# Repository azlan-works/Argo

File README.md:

# Argo v2

## Crowdsupply:

Argo is soon to launch on CrowdSupply, sign up now to be updated as soon as it's live and ready for pre-order!

https://www.crowdsupply.com/azlan-works/argo-cm5

## Mainboard
The main board houses the CM5 and breaks out the most basic functionality needed.

- 2x 100pin Hirose Connectors
- 2x MIPI-DSI/CSI
- 1x Micro-HDMI
- 1x HDMI FPC connector for external break out
- 1x PCIe FPC connector, Pi 5 compatible
- 2x USB-C (One for power/flashing - USB 2.0 and one regular USB 3.0)
- Integrated BMS (BQ25895) with up to 5A charging dependent on battery used.
- TPS61022 5V boost for upto 3A of constant power from battery or USB.
- I2C control for BQ25895 with ADC battery level monitoring.
- Onboard LSM6DSV16XTR IMU via I2C

Read more about the mainboard [here](./mainboard.md)
## Benchmarks:

Benchmarks conducted using v1 boards using CM5 16GB RAM and 64GB eMMC + Waveshare CM5 cooler with fan.

### On Adapter:

### On Battery:

## Expansion Boards:

### M.2 PCIe Expansion:
- Adds an M.2 M-Key Slot for external SSD
Read more about the SSD board [here](./ssdboard.md)

### Impedance Calculations:

### OSHWA Certification:

## Sponsored by OSHWLab Stars:
 &nbsp;

 </br>
 </br>
 
   &nbsp; &nbsp; &nbsp; &nbsp; &nbsp;  
 &nbsp;
  &nbsp;
   &nbsp;

</br></br>

Huge thanks to Bob from OSHWLab for all the support and sponsoring the PCBA! 

## Note:

Commerical reproduction is NOT permitted for this design without prior agreements.

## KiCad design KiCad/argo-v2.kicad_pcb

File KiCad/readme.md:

This KiCad project is just an export of the OSHWLab project, details may not match 100%

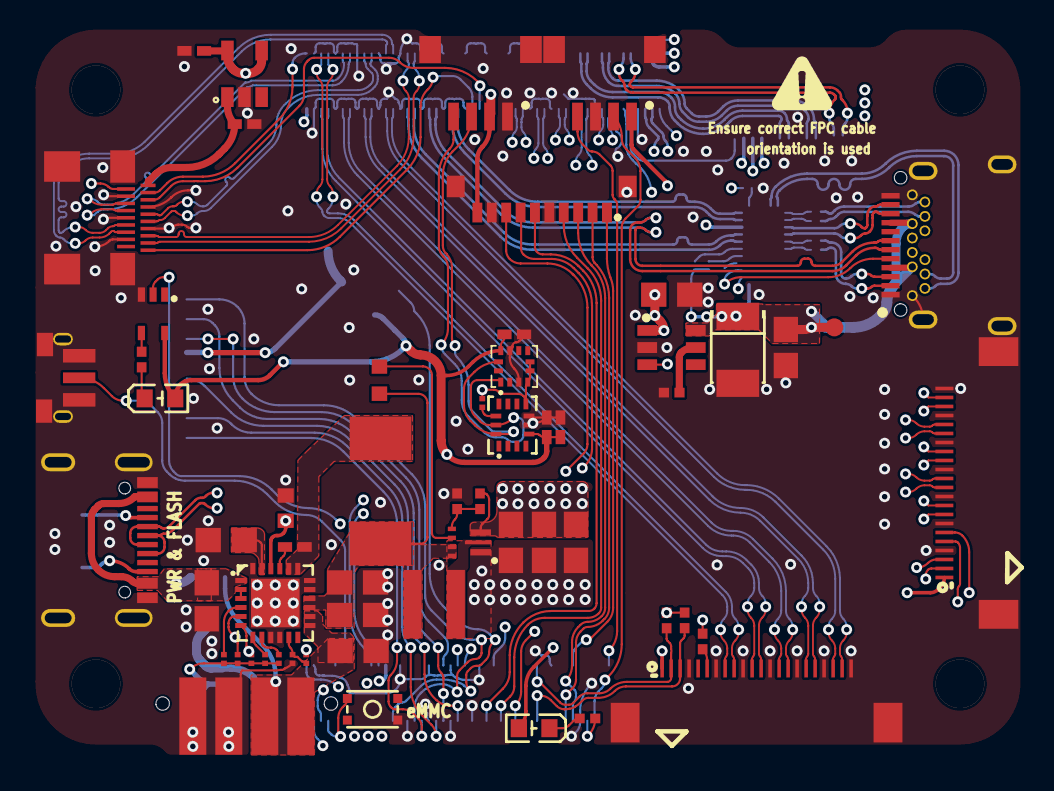
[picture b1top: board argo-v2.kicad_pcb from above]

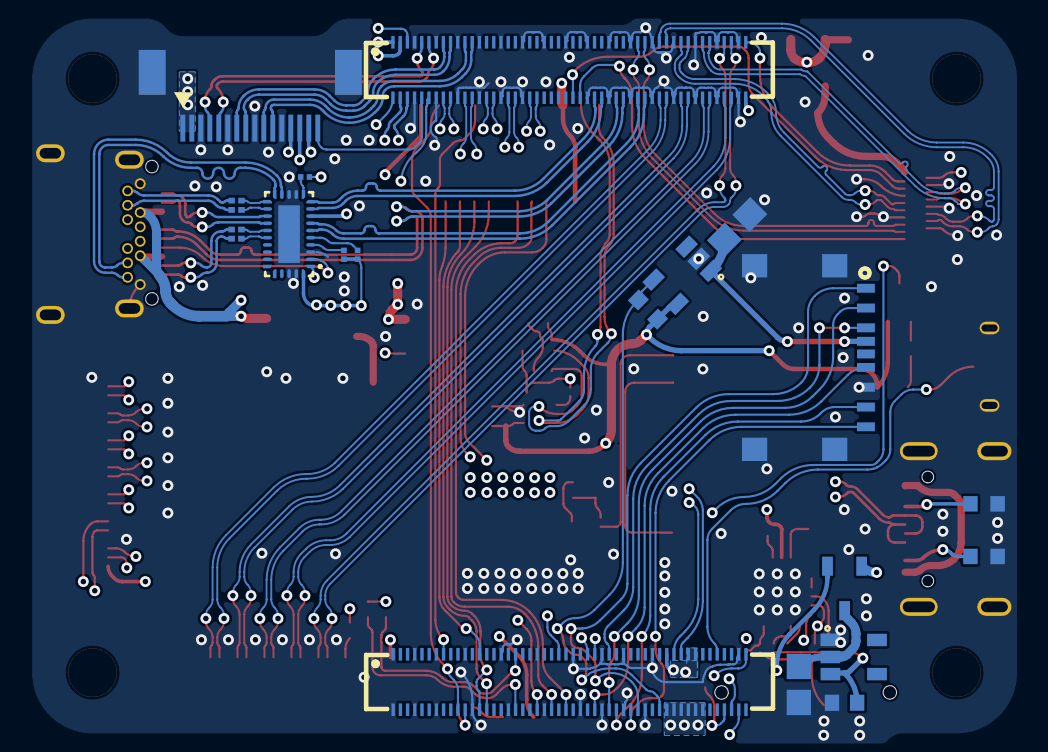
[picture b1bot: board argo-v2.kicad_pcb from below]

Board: 6 copper layers, 79 parts (22 on the bottom side), 127 nets.

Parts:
C1, C2, C30, C51, C52, C55, C58, C66, C69, C74, C75, C76: C0805
C3, C59: C0603
C4, C40, C41, C77, C78, C81: C0402
C53: CASE-B_3528
C70, C71, C72, C73: C0201
CN1, CN2: CONN-SMD_DF40HC-3.0-100DS-0.4V-51
CN6: CONN-SMD_GT-BTR20004-0250A-005A
D2: SOT-23-3_L2.9-W1.6-P1.90-LS2.8-BR
DPHY1, DPHY2: FPC-SMD_22P-P0.50_FH12-22S-0.5SH-55
FAN: CONN-SMD_4P-P1.00_SM04B-SRSS-TB-LF-SN
HDMI1: HDMI-SMD_HDMI-101W
I2C: CONN-SMD_4P-P1.00_SM04B-SRSS-TB-LF-SN
L1: IND-SMD_L6.5-W6.5_IHLP-2525
LED1: LED0603-FD
MODULE1: CM5IO{colon}Raspberry-Pi-5-Compute-Module
PCIe: FPC-SMD_16P-P0.50_HC-FPC-05-20-16RLTAG
PWR: USB-C-SMD_TYPEC-304J-BCP16
R6, R7, R12, R50: R0603
R29, R30, R31, R32, R34, R38, R51, R52: R0402
R39, R40, R41, R42, R43, R44, R45, R46, R47, R48, R53: R0201
SD-CARD: TF-SMD_TF-123-ARP9H15
SPI: CONN-SMD_10P-P0.80_HDGC0802WV-S-10P
SW2: KEY-SMD_4P-L2.8-W2.0-P1.20-LS3.0-TL
SW3: KEY-SMD_TS35CA-100GF-031
U7, U11, U13: TSOT-23-5_L2.9-W1.6-P0.95-LS2.8-BR
U9: QFN-24_L4.0-W4.0-P0.50-TL-EP2.7
U12: SOT-23-6_L2.9-W1.6-P0.95-LS2.8-BR
U14: LED0603-FD
U16: SC-88A_L2.0-W1.3-P0.65-LS2.1-BL
U20: VQFN-7_L2.0-W2.0-P0.55-TL_RWU
U21: IND-SMD_L4.1-W4.1_PA5430
U22: WQFN-30_L4.5-W2.5-P0.4-BL-EP
U23: LGA-14_L3.0-W2.5-P0.50-BR
U24: LGA-12_L2.0-W2.0-P0.50-BL
USB-C3.0: USB-C-SMD_TYPEC-324-BCP24

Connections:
$1N10774: R29.2, U14.2
$1N12706: R34.1, U16.4
$1N12751: LED1.2, R34.2
$2N4744: C4.1, U9.21
$2N5637: R44.2, R45.1, U9.11
$2N10575: U9.2, U9.3
$2N18023: C55.2, U9.23
$2N19126: PWR.A5, R6.1
$2N19130: PWR.B5, R7.1
$2N22099: R43.2, U9.8
$2N22411: C58.1, D2.3, U13.2
$2N49032: C4.2, L1.1, U9.19, U9.20
$2N49283: U20.2, U21.1
$2N51141: R50.1, U20.5
$2N51424: R38.2, R52.2, U20.4
$3N4264: DPHY2.6, R30.2
$4N5235: C41.2, HDMI1.19, U11.1
$4N37129: R53.1, U23.12
$5N11984: R51.1, U12.5
$5N17176: R46.1, U22.11
$5N17396: C73.1, U22.20
$5N17400: C72.1, U22.21
$5N17408: C70.1, U22.17
$5N17508: R47.2, U22.5
$5N17549: R48.2, U22.4
$5N17793: C71.1, U22.16
+3V3: C77.2, C78.2, C81.2, CN1.39, CN1.42, CN1.43, DPHY1.1, DPHY2.1, I2C.2, LED1.1, R12.1, R30.1, R31.1, R32.1, R46.2, R53.2, SPI.10, U7.5, U14.1, U16.5, U22.8, U23.5, U23.8, U24.4, U24.5, U24.6, U24.10
+5V: C40.1, C51.1, C66.2, C75.2, C76.2, CN1.57, CN1.58, CN1.59, CN1.60, CN1.61, CN1.62, PCIe.1, PCIe.2, R52.1, U11.4, U11.5, U12.1, U20.3
BAT+: C69.1, CN6.1, CN6.2, D2.2, U9.13, U9.14
CAM_GPIO0: CN1.52, DPHY1.6
CAM_GPIO1: CN1.50, DPHY1.5
CHG_INT: R42.2, U9.7
CRX1_N: U22.15, USB-C3.0.B10
CRX1_P: U22.14, USB-C3.0.B11
CRX2_N: U22.19, USB-C3.0.A10
CRX2_P: U22.18, USB-C3.0.A11
CTX1_N: C73.2, USB-C3.0.A3
CTX1_P: C72.2, USB-C3.0.A2
CTX2_N: C70.2, USB-C3.0.B3
CTX2_P: C71.2, USB-C3.0.B2
FAN_PWM: CN1.91, FAN.2
GND: C1.1, C2.1, C3.1, C30.1, C40.2, C41.1, C51.2, C52.1, C53.2, C55.1, C58.2, C59.2, C66.1, C69.2, C74.2, C75.1, C76.1, C77.1, C78.1, C81.1, CN1.1, CN1.4, CN1.7, CN1.11, CN1.16, CN1.21, CN1.26, CN1.30, CN1.33, CN1.37, CN1.49, CN1.65, CN1.68, CN1.71, CN1.74, CN1.79, CN1.84, CN1.89, CN1.94, CN1.97, CN1.100, CN2.4, CN2.7, CN2.10, CN2.13, CN2.16, CN2.19, CN2.22, CN2.25, CN2.28, CN2.31, CN2.34, CN2.37, CN2.40, CN2.43, CN2.46, CN2.49, CN2.52, CN2.55, CN2.58, CN2.61, CN2.64, CN2.67, CN2.70, CN2.73, CN2.82, CN2.85, CN2.88, CN2.91, CN2.94, CN2.97, CN6.3, CN6.4, DPHY1.4, DPHY1.7, DPHY1.10, DPHY1.13, DPHY1.16, DPHY1.19, DPHY1.22, DPHY1.23, DPHY1.24, DPHY2.4, DPHY2.7, DPHY2.10, DPHY2.13, DPHY2.16, DPHY2.19, DPHY2.22, DPHY2.23, DPHY2.24, FAN.3, FAN.5, FAN.6, HDMI1.4, HDMI1.7, HDMI1.10, HDMI1.13, HDMI1.16, HDMI1.20, I2C.1, I2C.5, I2C.6, PCIe.3, PCIe.6, PCIe.9, PCIe.12, PCIe.17, PCIe.18, PWR.13, PWR.14, PWR.15, PWR.16, PWR.A1B12, PWR.B1A12, R6.2, R7.2, R38.1, R44.1, R51.2, SD-CARD.6, SD-CARD.10, SD-CARD.11, SD-CARD.12, SD-CARD.13, SPI.5, SPI.9, SPI.11, SPI.12, SW2.4, SW3.1, SW3.3, SW3.4, U7.2, U9.9, U9.10, U9.17, U9.18, U9.24, U9.25, U11.2, U12.2, U13.1, U16.3, U20.1, U22.3, U22.12, U22.13, U22.28, U22.29, U22.31, U23.6, U23.7, U24.3, U24.9, USB-C3.0.1, USB-C3.0.2, USB-C3.0.3, USB-C3.0.4, USB-C3.0.A1, USB-C3.0.A12, USB-C3.0.B1, USB-C3.0.B12
GPIO2: CN1.29, I2C.3, R41.2, U9.6, U23.14, U24.11
GPIO3: CN1.28, I2C.4, R40.2, U9.5, U23.13, U24.1
GPIO18: CN1.76, SPI.6
GPIO19: CN1.13, SPI.1
GPIO20: CN1.87, SPI.2
GPIO21: CN1.88, SPI.3
GPIO24: CN1.78, SPI.4
GPIO25: CN1.80, SPI.8
GPIO27: CN1.24, SPI.7
HDMI0_CEC: CN2.75, HDMI1.15
HDMI0_CLK_N: CN2.45, HDMI1.14
HDMI0_CLK_P: CN2.44, HDMI1.12
HDMI0_HOTPLUG: CN2.74, HDMI1.1
HDMI0_SCL: CN2.50, HDMI1.17
HDMI0_SDA: CN2.51, HDMI1.18
HDMI0_TX0_N: CN2.42, HDMI1.11
HDMI0_TX0_P: CN2.41, HDMI1.9
HDMI0_TX1_N: CN2.39, HDMI1.8
HDMI0_TX1_P: CN2.38, HDMI1.6
HDMI0_TX2_N: CN2.36, HDMI1.5
HDMI0_TX2_P: CN2.35, HDMI1.3
ID_SC: CN1.83, DPHY2.3, R31.2
ID_SD: CN1.18, DPHY2.2, R32.2
LED_NACT: CN1.90, R29.1
LED_NPWR: CN1.53, U16.2
MIPI0_C_N: CN2.87, DPHY1.15
MIPI0_C_P: CN2.86, DPHY1.14
MIPI0_D0_N: CN2.93, DPHY1.21
MIPI0_D0_P: CN2.92, DPHY1.20
MIPI0_D1_N: CN2.90, DPHY1.18
MIPI0_D1_P: CN2.89, DPHY1.17
MIPI0_D2_N: CN2.84, DPHY1.12
MIPI0_D2_P: CN2.83, DPHY1.11
MIPI0_D3_N: CN2.81, DPHY1.9
MIPI0_D3_P: CN2.80, DPHY1.8
MIPI1_C_N: CN2.57, DPHY2.15
MIPI1_C_P: CN2.56, DPHY2.14
MIPI1_D0_N: CN2.63, DPHY2.21
MIPI1_D0_P: CN2.62, DPHY2.20
MIPI1_D1_N: CN2.60, DPHY2.18
MIPI1_D1_P: CN2.59, DPHY2.17
MIPI1_D2_N: CN2.54, DPHY2.12
MIPI1_D2_P: CN2.53, DPHY2.11
MIPI1_D3_N: CN2.47, DPHY2.9
MIPI1_D3_P: CN2.48, DPHY2.8
NRPIBOOT: CN1.54, SW2.1
OCC1: U22.2, USB-C3.0.A5
OCC2: U22.1, USB-C3.0.B5
PCIE_CLK_N: CN2.6, PCIe.5
PCIE_CLK_P: CN2.5, PCIe.4
PCIE_NCLKREQ: CN2.1, PCIe.15
PCIE_NRESET: CN2.96, PCIe.16
PCIE_NWAKE: CN2.2, PCIe.14
PCIE_PWR_EN: CN2.3, PCIe.13
PCIE_RX_N: CN2.9, PCIe.8
PCIE_RX_P: CN2.8, PCIe.7
PCIE_TX_N: CN2.12, PCIe.11
PCIE_TX_P: CN2.11, PCIe.10
PWR_BUTTON: CN1.46, SW3.2
REGN: C3.2, R45.2, U9.22
SCL0: CN1.40, DPHY1.3
SDA0: CN1.41, DPHY1.2
SD_CLK: CN1.72, SD-CARD.5
SD_CMD: CN1.31, SD-CARD.3
SD_DAT0: CN1.69, SD-CARD.7
SD_DAT1: CN1.67, SD-CARD.8
SD_DAT2: CN1.66, SD-CARD.1
SD_DAT3: CN1.70, SD-CARD.2
SD_PWR: C30.2, SD-CARD.4, U7.1
SD_PWR_ON: CN1.63, R12.2, U7.4
STAT: R39.2, U9.4
TACHO: CN1.8, FAN.4
USB2_N: CN2.99, PWR.A7, PWR.B7
USB2_P: CN2.98, PWR.A6, PWR.B6
USB31_D_N: CN2.68, USB-C3.0.A7, USB-C3.0.B7
USB31_D_P: CN2.69, USB-C3.0.A6, USB-C3.0.B6
USB31_RX_N: CN2.72, U22.10
USB31_RX_P: CN2.71, U22.9
USB31_TX_N: CN2.66, U22.7
USB31_TX_P: CN2.65, U22.6
VBUS: C1.2, D2.1, PWR.A4B9, PWR.B4A9, U9.1
VBUS_EN: CN2.95, U12.3
VREF: C59.1, R39.1, R40.1, R41.1, R42.1, R43.1, U13.3
VSYS: C2.2, C74.1, L1.2, R50.2, U9.15, U9.16, U20.6, U20.7, U21.2
VUSB: C52.2, C53.1, FAN.1, R47.1, R48.1, U12.6, U22.30, USB-C3.0.A4, USB-C3.0.A9, USB-C3.0.B4, USB-C3.0.B9

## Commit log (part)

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2025-09-13 Update README to reflect sponsorship changes
    Removed an image from the README and added sponsorship acknowledgment.
2025-09-13 Remove unused images from README
    Removed three images from the README file.
2025-09-14 Remove layer images from mainboard.md
2025-09-19 Enhance README with additional information
    Added a new line for clarity in the README.
2025-09-19 Reduce image width in README.md
2025-10-02 Fix typo in commercial reproduction note
2026-03-23 Refactor battery voltage monitoring functions
